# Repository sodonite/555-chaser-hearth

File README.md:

I made this project through a Hackclub workshop, It has 10 different color LED's that flash in sequence named blinky board 
I did this mainly to explore KiCad's features and learn how to use it with this basic project
https://blueprint.hackclub.com/starter-projects/blinky
This is the project schematic.
It is very important to wire this correctly so that the device works properly at the correct voltage.

This is how it would look in the KiCad 3D model,but the difference from other projects or from the original instructions is that I wanted to have a printed circuit board with the LEDs on one side and the entire circuit with the other components on the other side.

And finally, here is a preview of what the PCB would look like on both sides

this is the BOM (Bill Of Materials)

10 LEDs: Light-emitting diodes for the heart display — $1.63 USD.

1 Trimmer (50kΩ): Potentiometer to manually adjust the heart's blink speed — $2.87 USD.

1 CD4017 IC: Decade counter that controls the LED sequence — $1.27 USD.

1 NE555P IC: Timer chip that generates the pulse for the circuit — $0.51 USD.

1 2-Pin Socket (J2): Connector for the battery/power input — $0.35 USD.

1 1-Pin Socket (J3): Single header for testing or mechanical support — $0.28 USD.

1 Capacitor (1uF): Electrolytic capacitor for timing stabilization — $0.28 USD.

1 Resistor (1000Ω / R1): Component used for timer configuration — $0.10 USD.

1 Resistor (470Ω / R3): Protection resistor to prevent burning the LEDs — $0.10 USD.

1 Capacitor (0.01uF): Ceramic disc capacitor to filter electrical noise — $0.10 USD.

# 555-chaser-hearth

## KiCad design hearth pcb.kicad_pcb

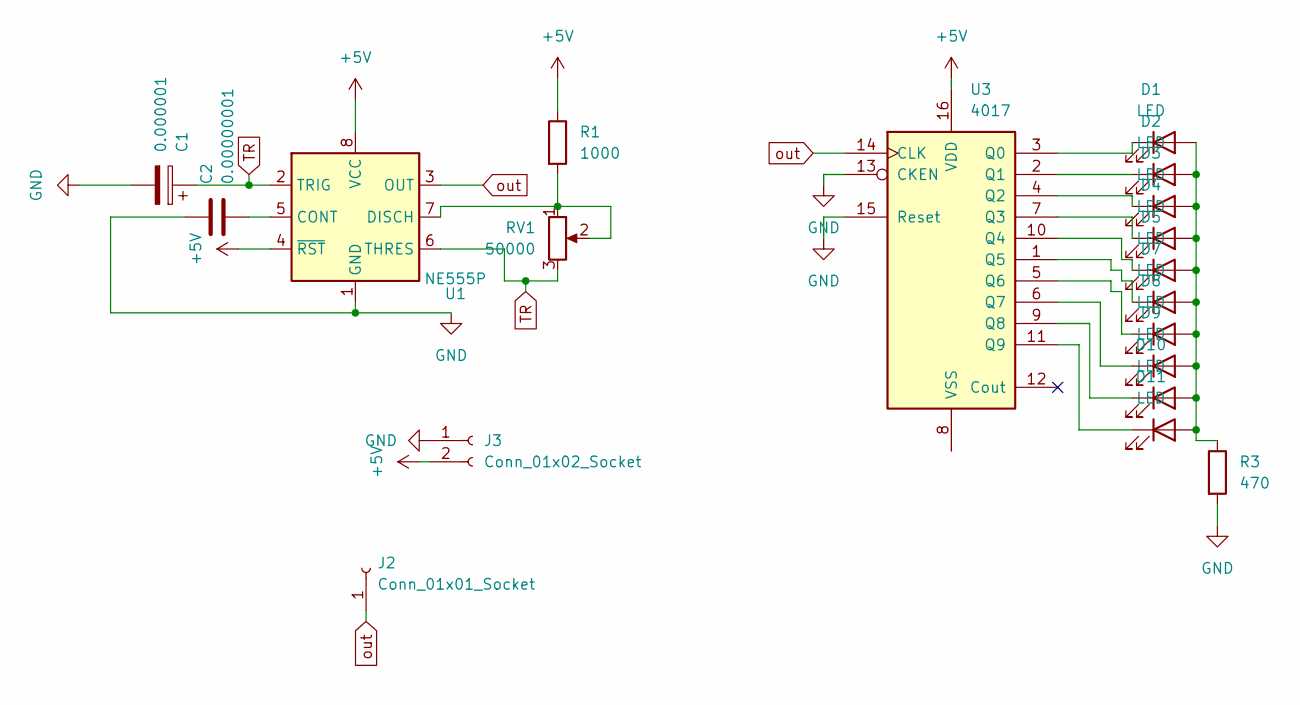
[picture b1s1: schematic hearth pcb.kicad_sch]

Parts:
C1: 0.000001; CP_Radial_D5.0mm_P2.00mm
C2: 0.00000001; CP_Radial_D5.0mm_P2.00mm
D1, D2, D3, D4, D5, D7, D8, D9, D10, D11: LED; LED_D5.0mm
J2: Conn_01x01_Socket; PinHeader_1x01_P2.54mm_Vertical
J3: Conn_01x02_Socket; PinHeader_1x02_P2.54mm_Vertical
R1: 1000; R_Axial_DIN0207_L6.3mm_D2.5mm_P7.62mm_Horizontal
R3: 470; R_Axial_DIN0207_L6.3mm_D2.5mm_P7.62mm_Horizontal
RV1: 50000; Potentiometer_Bourns_3299W_Vertical
U1: NE555P; DIP-8_W7.62mm
U3: 4017

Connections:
+5V: J3.2, R1.1, U1.4 (~RST), U1.8 (VCC), U3.16 (VDD)
GND: C1.2, C2.1, J3.1, R3.2, U1.1 (GND), U3.13 (CKEN), U3.15 (Reset)
unnamed: D1.2 (A), D2.2 (A), D3.2 (A), D4.2 (A), D5.2 (A), D7.2 (A), D8.2 (A), D9.2 (A), D10.2 (A), D11.2 (A), R3.1
unnamed: D1.1 (K), U3.3 (Q0)
unnamed: D2.1 (K), U3.2 (Q1)
unnamed: D3.1 (K), U3.4 (Q2)
unnamed: D4.1 (K), U3.7 (Q3)
unnamed: D5.1 (K), U3.10 (Q4)
unnamed: D7.1 (K), U3.1 (Q5)
unnamed: D8.1 (K), U3.5 (Q6)
unnamed: D9.1 (K), U3.6 (Q7)
unnamed: D10.1 (K), U3.9 (Q8)
unnamed: D11.1 (K), U3.11 (Q9)
unnamed: C2.2, U1.5 (CONT)
unnamed: R1.2, RV1.1, RV1.2, U1.7 (DISCH)
TR: C1.1, RV1.3, U1.2 (TRIG), U1.6 (THRES)
out: J2.1 (Pin_1_1), U1.3 (OUT), U3.14 (CLK)

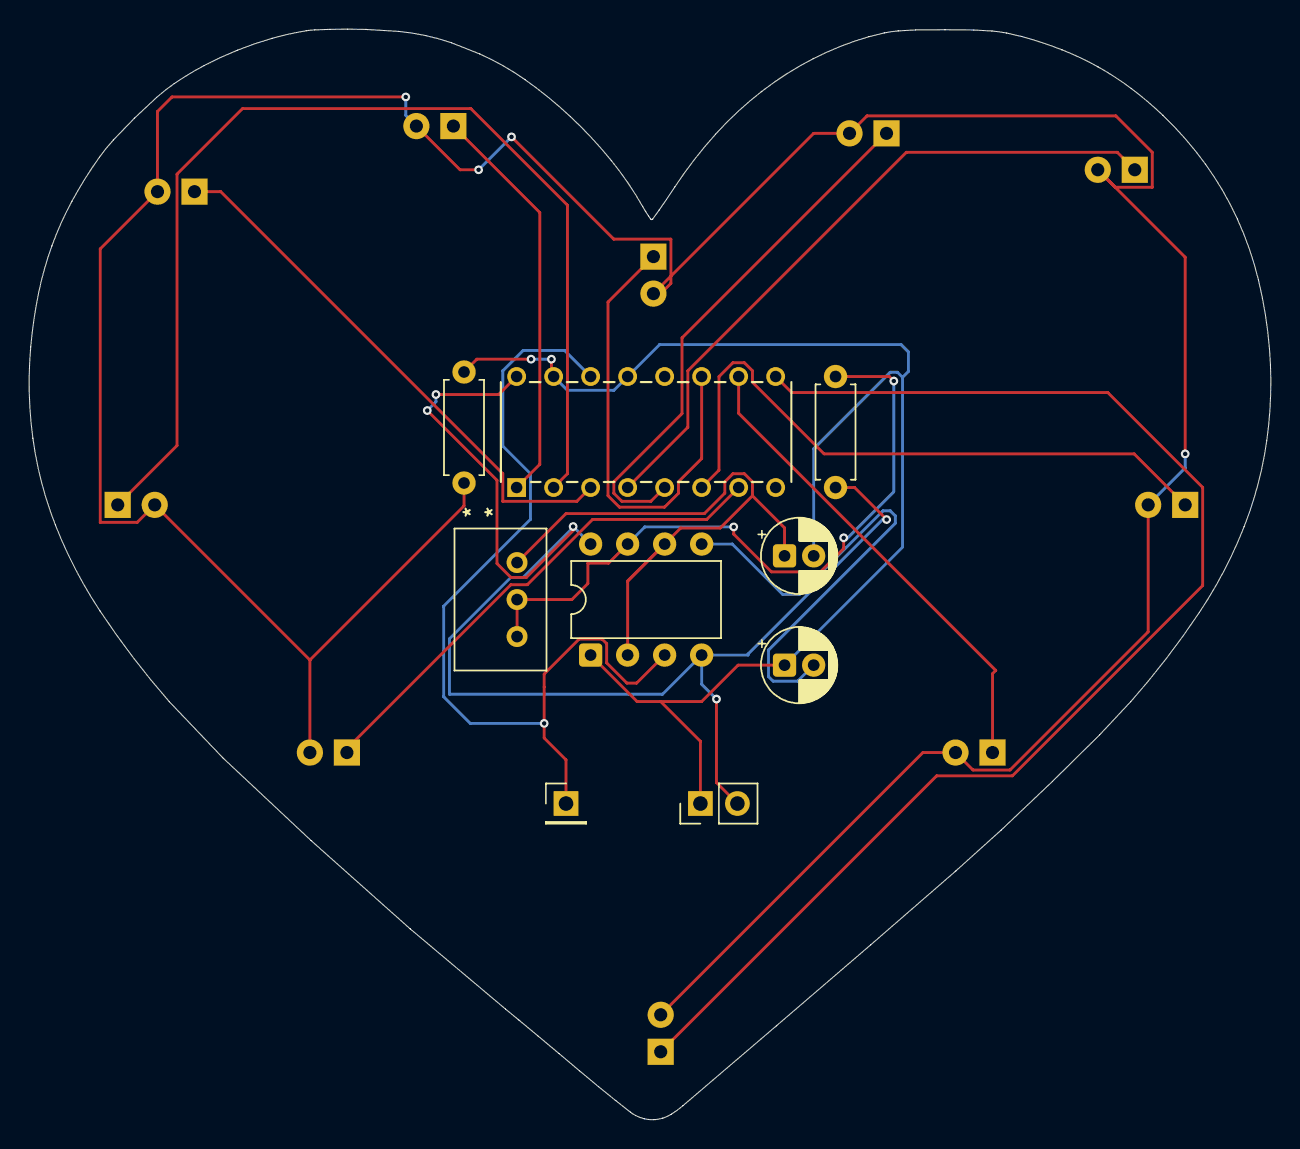
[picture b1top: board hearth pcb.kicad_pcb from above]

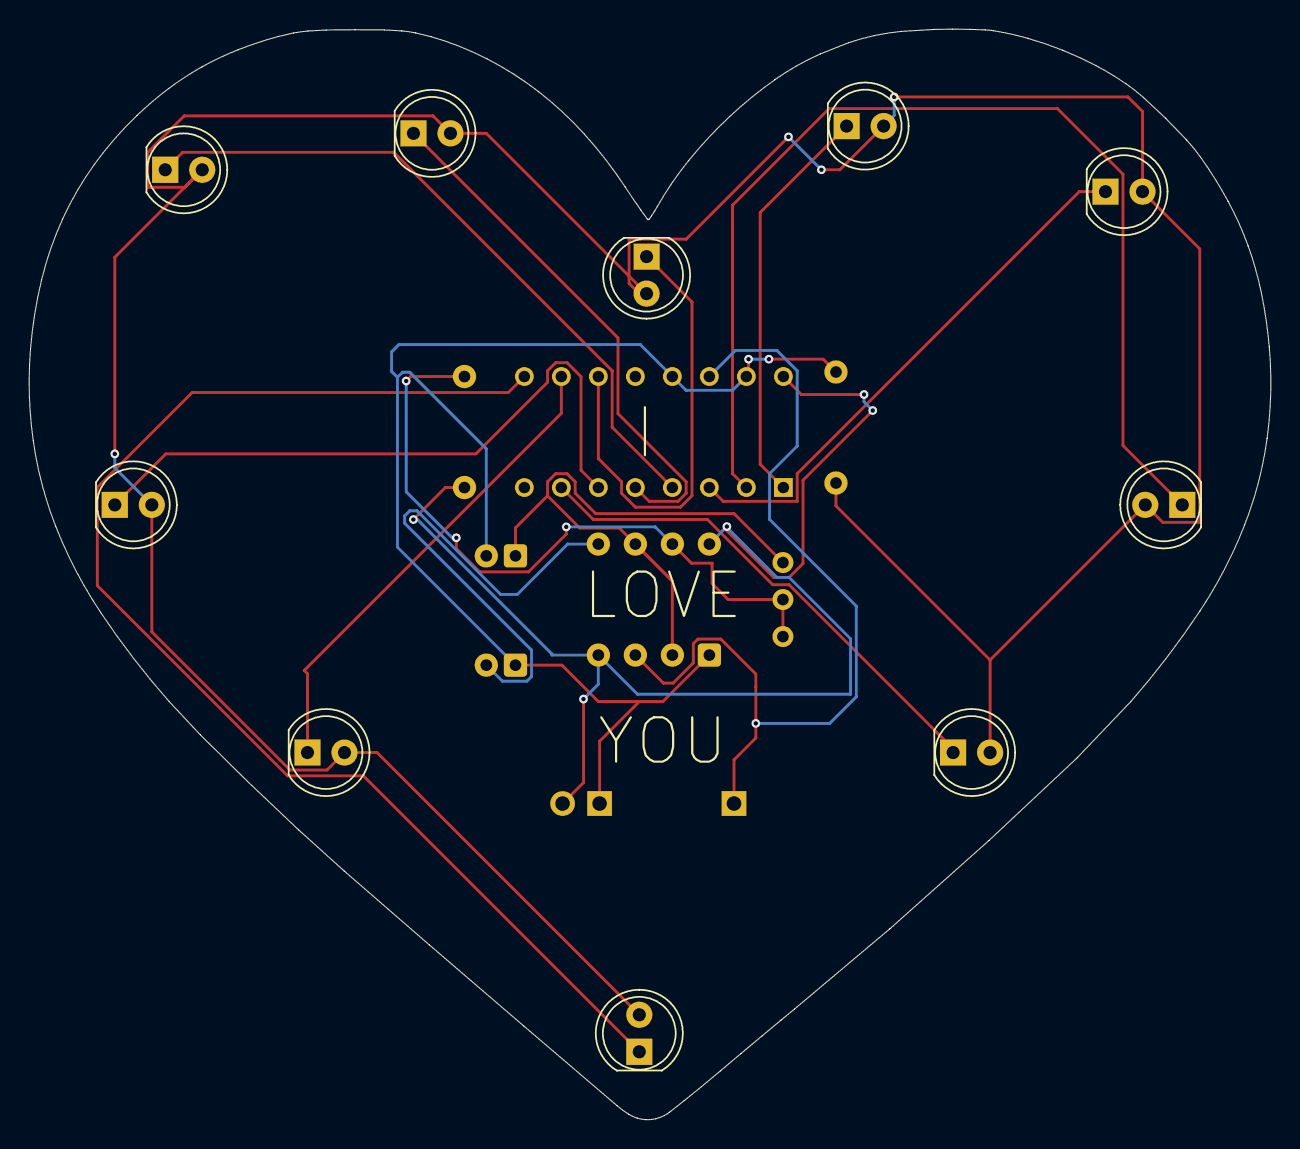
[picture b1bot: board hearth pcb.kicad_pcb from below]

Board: 2 copper layers, 85.2 x 74.9 mm, 19 parts (10 on the bottom side), 17 nets.

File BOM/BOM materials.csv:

Name,Purpose,Quantity,Total Cost (USD),Link,Distributor
"leds","",10,1.63,"",""
"Conn_01x02_Socket","",1,0.35,"",""
"Conn_01x01_Socket","",1,0.28,"",""
"Resistor","1000ohms",1,0.10,"",""
"TRIMMER ","50K OHM",1,2.87,"",""
"CD4017","",1,1.27,"",""
"Capacithor","1uF",1,0.28,"",""
"Resistor","470ohms",1,0.10,"",""
"NE555P","",1,0.51,"",""
"Capacithor","0.01uF",1,0.10,"",""

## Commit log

2026-04-29 Create BOM
2026-04-29 Create BOM materials
2026-04-29 Rename HEARTH LED-bom (1).csv to BOM materials.csv
2026-04-29 Create Files hearth pcb
2026-04-29 Create w
